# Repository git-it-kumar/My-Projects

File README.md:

Here are some projects which have been developed using the fundamental concepts and have been catagorized accordingly.

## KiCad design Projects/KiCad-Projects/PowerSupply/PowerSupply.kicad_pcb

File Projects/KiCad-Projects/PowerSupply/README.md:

This is a PCB design of a circuit which provides a power supply of 5V DC as an ouput after converting an AC input. This project has been developed using the KiCad IDE software

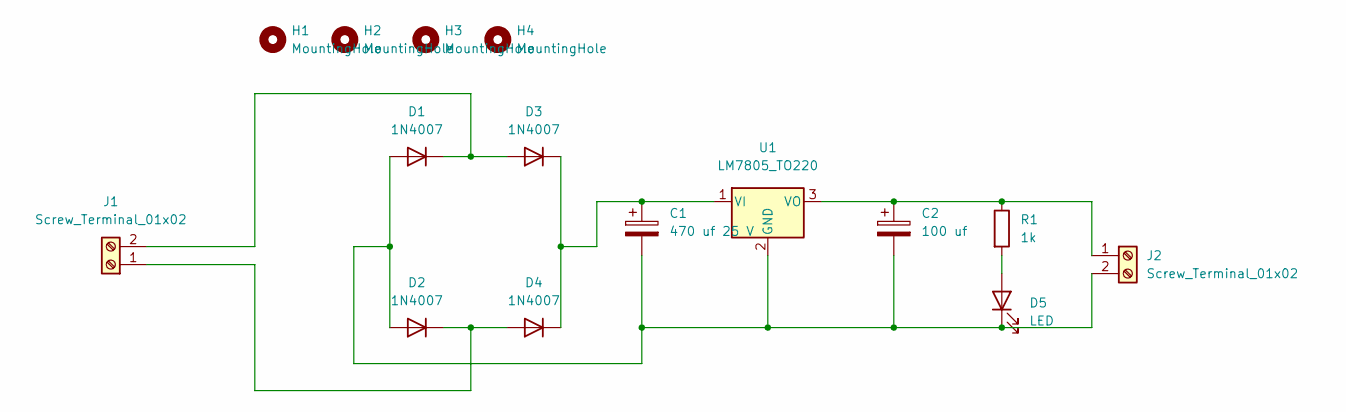
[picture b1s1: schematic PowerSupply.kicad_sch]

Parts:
C1: 470 uf 25 V; CP_Radial_D4.0mm_P1.50mm
C2: 100 uf; CP_Radial_D4.0mm_P1.50mm
D1, D2, D3, D4: 1N4007; D_DO-41_SOD81_P10.16mm_Horizontal
D5: LED; LED_D3.0mm
H1, H2, H3, H4: MountingHole; MountingHole_2.7mm_M2.5
J1, J2: Screw_Terminal_01x02; TerminalBlock_bornier-2_P5.08mm
R1: 1k; R_Axial_DIN0204_L3.6mm_D1.6mm_P5.08mm_Horizontal
U1: LM7805_TO220; TO-220-3_Vertical

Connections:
unnamed: C1.1, D3.1 (K), D4.1 (K), U1.1 (VI)
unnamed: C1.2, C2.2, D1.2 (A), D2.2 (A), D5.1 (K), J2.2, U1.2 (GND)
unnamed: C2.1, J2.1, R1.1, U1.3 (VO)
unnamed: D1.1 (K), D3.2 (A), J1.2
unnamed: D2.1 (K), D4.2 (A), J1.1
unnamed: D5.2 (A), R1.2

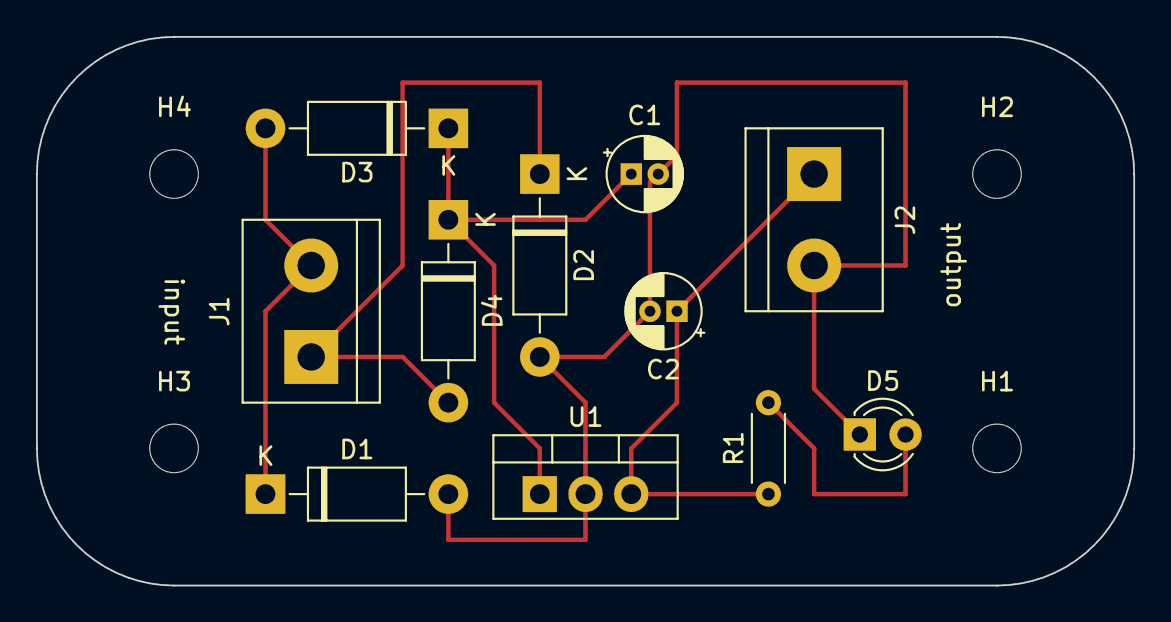
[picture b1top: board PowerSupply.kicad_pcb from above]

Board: 2 copper layers, 61.0 x 30.5 mm, 15 parts (0 on the bottom side), 6 nets.

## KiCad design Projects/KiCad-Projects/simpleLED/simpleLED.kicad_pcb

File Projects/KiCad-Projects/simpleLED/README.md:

This is the PCB design of a simple circuit which contains a terminal to attach a battery, a resistor and an LED

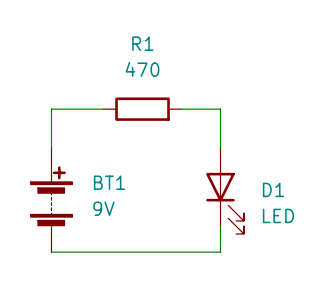
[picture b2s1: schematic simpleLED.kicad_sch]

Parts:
BT1: 9V; PinHeader_1x02_P2.54mm_Vertical
D1: LED; LED_D5.0mm
R1: 470; R_Axial_DIN0207_L6.3mm_D2.5mm_P15.24mm_Horizontal

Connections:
unnamed: BT1.1 (+), R1.1
unnamed: BT1.2 (-), D1.1 (K)
unnamed: D1.2 (A), R1.2

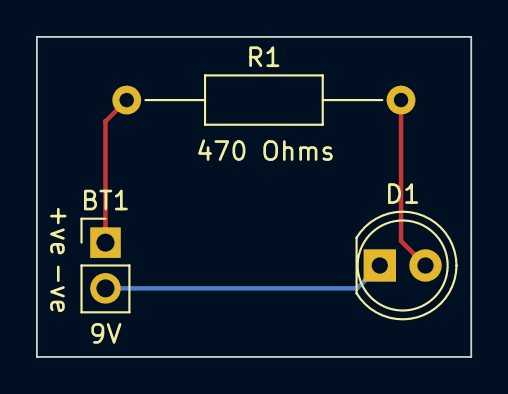
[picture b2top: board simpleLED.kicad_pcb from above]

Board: 2 copper layers, 24.1 x 17.8 mm, 3 parts (0 on the bottom side), 3 nets.

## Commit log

2023-01-29 Create KiCad-Projects
